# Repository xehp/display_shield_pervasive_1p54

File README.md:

# display_shield_pervasive_1p54
shield for pervasive display 1.54" EPD, A-MB, W.ITC

This aims to design a shield for the Pervasive Displays 1.54" EPD, A-MB, W.ITC E2154CS0C1.

The intention is to make a design that can be sent to JLCPCB for PCB and SMA manufactoring.

It is a work in progress. I usually bunch a few projects together since delivery is a large
part of the cost when ordering the PCB/SMA. So this project will finish when some other minor projects also are ready.
If someone is interested in this particular one I could speed it up a bit.

See also "kicad/schematic.pdf".

/Henrik

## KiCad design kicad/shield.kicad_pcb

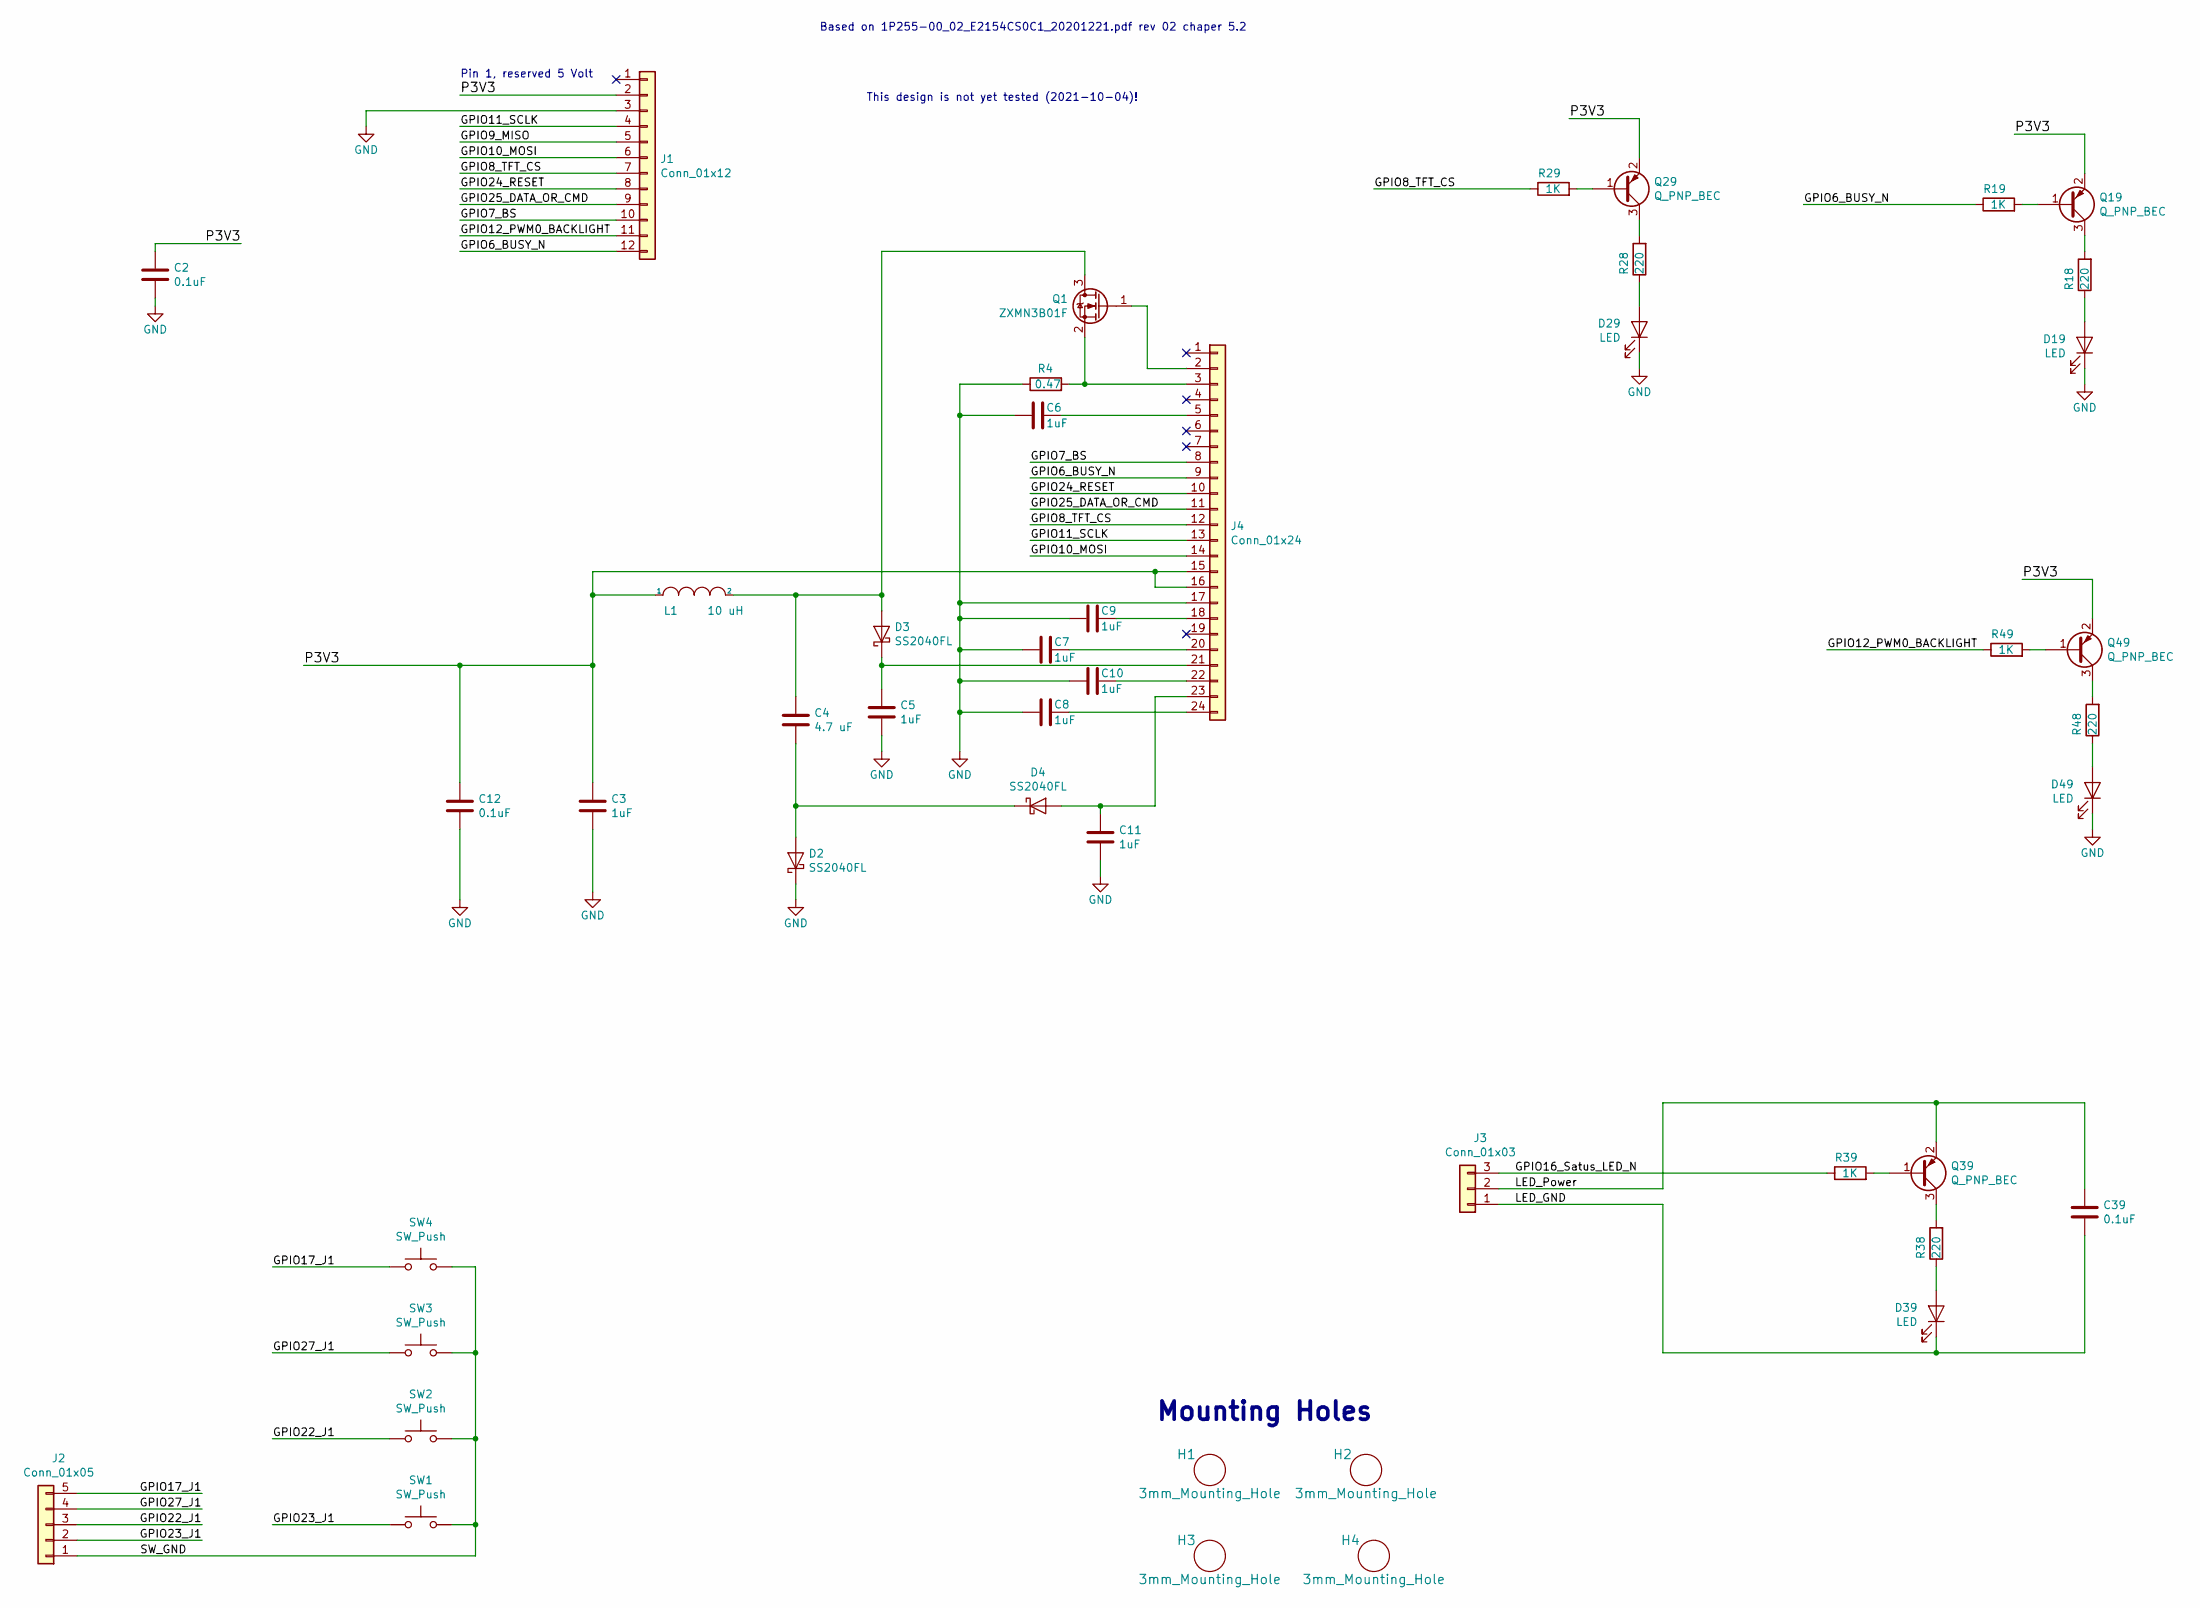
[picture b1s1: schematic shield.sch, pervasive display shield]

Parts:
C2, C12, C39: 0.1uF; C_0805_2012Metric
C3, C5, C6, C7, C8, C9, C10, C11: 1uF; C_0805_2012Metric
C4: 4.7 uF; C_1206_3216Metric
D2, D3, D4: SS2040FL; D_SOD-123F
D19, D29, D39, D49: LED; LED_D3.0mm
H1, H2, H3, H4: 3mm_Mounting_Hole; NPTH_3mm_ID
J1: Conn_01x12; PinHeader_1x12_P2.54mm_Vertical
J2: Conn_01x05; PinHeader_1x05_P2.54mm_Vertical
J3: Conn_01x03; PinHeader_1x03_P2.54mm_Vertical
J4: Conn_01x24; Hirose_FH12-24S-0.5SH_1x24-1MP_P0.50mm_Horizontal
L1: 10 uH; L_1206_3216Metric
Q1: ZXMN3B01F; SOT-23
Q19, Q29, Q39, Q49: Q_PNP_BEC; SOT-23
R4: 0.47; R_0805_2012Metric_Pad1.15x1.40mm_HandSolder
R18, R28, R38, R48: 220; R_0805_2012Metric_Pad1.15x1.40mm_HandSolder
R19, R29, R39, R49: 1K; R_0805_2012Metric_Pad1.15x1.40mm_HandSolder
SW1, SW2, SW3, SW4: SW_Push; SW_TH_Tactile_Omron_B3F-10xx

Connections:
/GPIO6_BUSY_N: J1.12, J4.9, R19.1
/GPIO7_BS: J1.10, J4.8
/GPIO8_TFT_CS: J1.7, J4.12, R29.1
/GPIO10_MOSI: J1.6, J4.14
/GPIO11_SCLK: J1.4, J4.13
/GPIO12_PWM0_BACKLIGHT: J1.11, R49.1
/GPIO16_Satus_LED_N: J3.3, R39.1
/GPIO17_J1: J2.5, SW4.1
/GPIO22_J1: J2.3, SW2.1
/GPIO23_J1: J2.2, SW1.1
/GPIO24_RESET: J1.8, J4.10
/GPIO25_DATA_OR_CMD: J1.9, J4.11
/GPIO27_J1: J2.4, SW3.1
/LED_GND: C39.2, D39.1 (K), J3.1
/LED_Power: C39.1, J3.2, Q39.2 (E)
/P3V3: C2.1, C3.1, C12.1, J1.2, J4.15, J4.16, L1.1, Q19.2 (E), Q29.2 (E), Q49.2 (E)
/SW_GND: J2.1, SW1.2, SW2.2, SW3.2, SW4.2
GND: C2.2, C3.2, C5.2, C6.2, C7.2, C8.2, C9.2, C10.2, C11.2, C12.2, D2.1 (K), D19.1 (K), D29.1 (K), D49.1 (K), J1.3, J4.17, R4.1
unnamed: C4.1, D3.2 (A), L1.2, Q1.3 (D)
unnamed: C4.2, D2.2 (A), D4.1 (K)
unnamed: C5.1, D3.1 (K), J4.21
unnamed: C6.1, J4.5
unnamed: C7.1, J4.20
unnamed: C8.1, J4.24
unnamed: C9.1, J4.18
unnamed: C10.1, J4.22
unnamed: C11.1, D4.2 (A), J4.23
unnamed: D19.2 (A), R18.1
unnamed: D29.2 (A), R28.1
unnamed: D39.2 (A), R38.1
unnamed: D49.2 (A), R48.1
unnamed: J4.2, Q1.1 (G)
unnamed: J4.3, Q1.2 (S), R4.2
unnamed: Q19.1 (B), R19.2
unnamed: Q19.3 (C), R18.2
unnamed: Q29.1 (B), R29.2
unnamed: Q29.3 (C), R28.2
unnamed: Q39.1 (B), R39.2
unnamed: Q39.3 (C), R38.2
unnamed: Q49.1 (B), R49.2
unnamed: Q49.3 (C), R48.2

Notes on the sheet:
Mounting Holes
Based on 1P255-00_02_E2154CS0C1_20201221.pdf rev 02 chaper 5.2
This design is not yet tested (2021-10-04)!
Pin 1, reserved 5 Volt

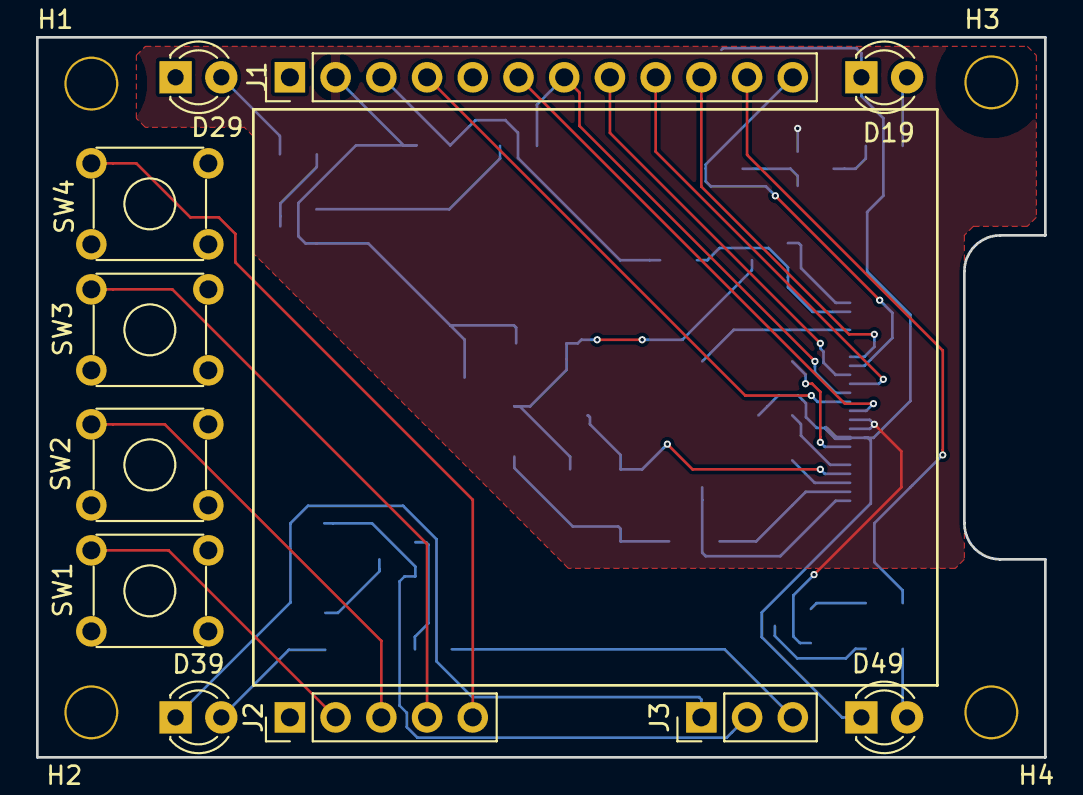
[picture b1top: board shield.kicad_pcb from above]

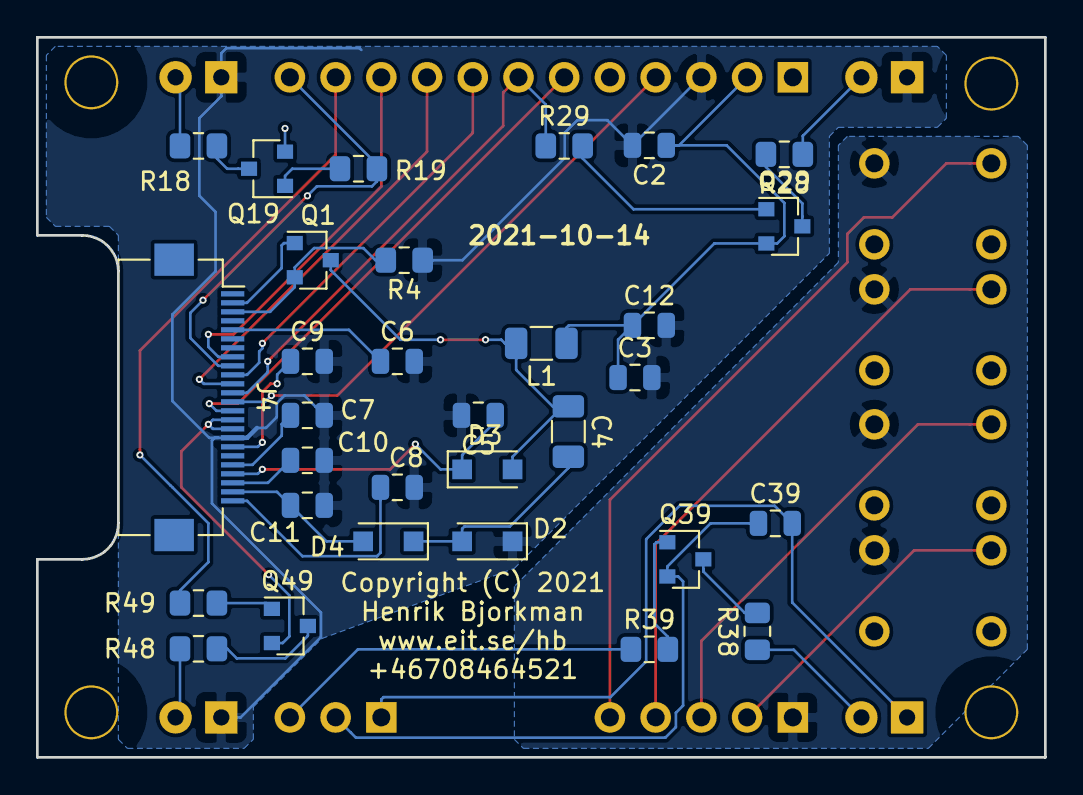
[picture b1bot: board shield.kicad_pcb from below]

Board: 2 copper layers, 56.0 x 40.0 mm, 46 parts (31 on the bottom side), 41 nets.

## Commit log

2021-10-06 Added kicad drawings (not finished)
2021-10-14 did routing, ready to be tested
2021-10-14 added kicad/schematic.pdf
2021-10-18 added power LED
2021-10-18 replaced power LED with a PWM LED

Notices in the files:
kicad/shield.kicad_pcb:
Copyright (C) 2021
